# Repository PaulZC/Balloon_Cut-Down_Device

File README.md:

# Balloon_Cut-Down_Device

A cut-down device suitable for use on High Altitude Balloons and other remote actuation projects.

Designed to be triggered by the [Iridium Beacon Radio Board](https://github.com/PaulZC/Iridium_Beacon_Radio_Board),
carried by the [Iridium 9603N V5 Beacon](https://github.com/PaulZC/Iridium_9603_Beacon), the cut-down will be triggered
when it receives its own (unique) serial number on the chosen radio channel. The number of cut-downs that could be
triggered by a single Iridium Beacon is essentially unlimited. The cut-down can also be configured to trigger at
a pre-defined altitude.

The device comprises:
- [Scott Archery Shark release aid](https://scottarchery.com/collections/releases/products/shark-release), actuated by a
- [HiTec HS-82MG servo](https://www.servoshop.co.uk/index.php?pid=HITHS82MG&area=Servo), controlled by the
- [LPRS eRIC4 or eRIC9 integrated radio module](http://www.lprs.co.uk/products/easyradio-ism-modules/eric-soc-rf-modules.html).
- The altitude is provided by a [u-blox CAM-M8Q GNSS receiver](https://www.u-blox.com/en/product/cam-m8-series)

See [LEARN.md](https://github.com/PaulZC/Balloon_Cut-Down_Device/blob/master/LEARN.md) for further details.

See [SERVO.md](https://github.com/PaulZC/Balloon_Cut-Down_Device/blob/master/SERVO.md) for details on how to modify the HiTec servo for
high altitude operation.

See [SHARK.md](https://github.com/PaulZC/Balloon_Cut-Down_Device/blob/master/SHARK.md) for details on how to incorporate the Scott Archery Shark release aid
into the Cut-Down Device.

See [ASSEMBLY.md](https://github.com/PaulZC/Balloon_Cut-Down_Device/blob/master/ASSEMBLY.md) for details on how to assemble the PCB and the device itself.

See [CONFIGURE.md](https://github.com/PaulZC/Balloon_Cut-Down_Device/blob/master/CONFIGURE.md) for details on how to configure the servo positions and altitude limit.

See [Balloon_Cut-Down_Device.pdf](https://github.com/PaulZC/Balloon_Cut-Down_Device/blob/master/Balloon_Cut-Down_Device.pdf) for the schematic,
layout and Bill Of Materials.

The [Eagle](https://github.com/PaulZC/Balloon_Cut-Down_Device/tree/master/Eagle) directory contains the schematic and pcb design files.

The [eRIC](https://github.com/PaulZC/Balloon_Cut-Down_Device/tree/master/eRIC) directory contains the code for the eRIC integrated radio module.

The [Drawings](https://github.com/PaulZC/Balloon_Cut-Down_Device/tree/master/Drawings) directory contains the drawings for the trigger linkage.

If you have found this project useful and if you are able to, please cite the paper:

P. Clark et al, An open source toolkit for the tracking, termination and recovery of high altitude balloon flights and payloads, 2019 JINST 14 P04003
[DOI:10.1088/1748-0221/14/04/P04003](https://doi.org/10.1088/1748-0221/14/04/P04003)

The Accepted Manuscript is available on arXiv: http://arxiv.org/abs/1904.04321

This project is distributed under a Creative Commons Attribution + Share-alike (BY-SA) licence.
Please refer to section 5 of the licence for the "Disclaimer of Warranties and Limitation of Liability".

Enjoy!

**_Paul_**

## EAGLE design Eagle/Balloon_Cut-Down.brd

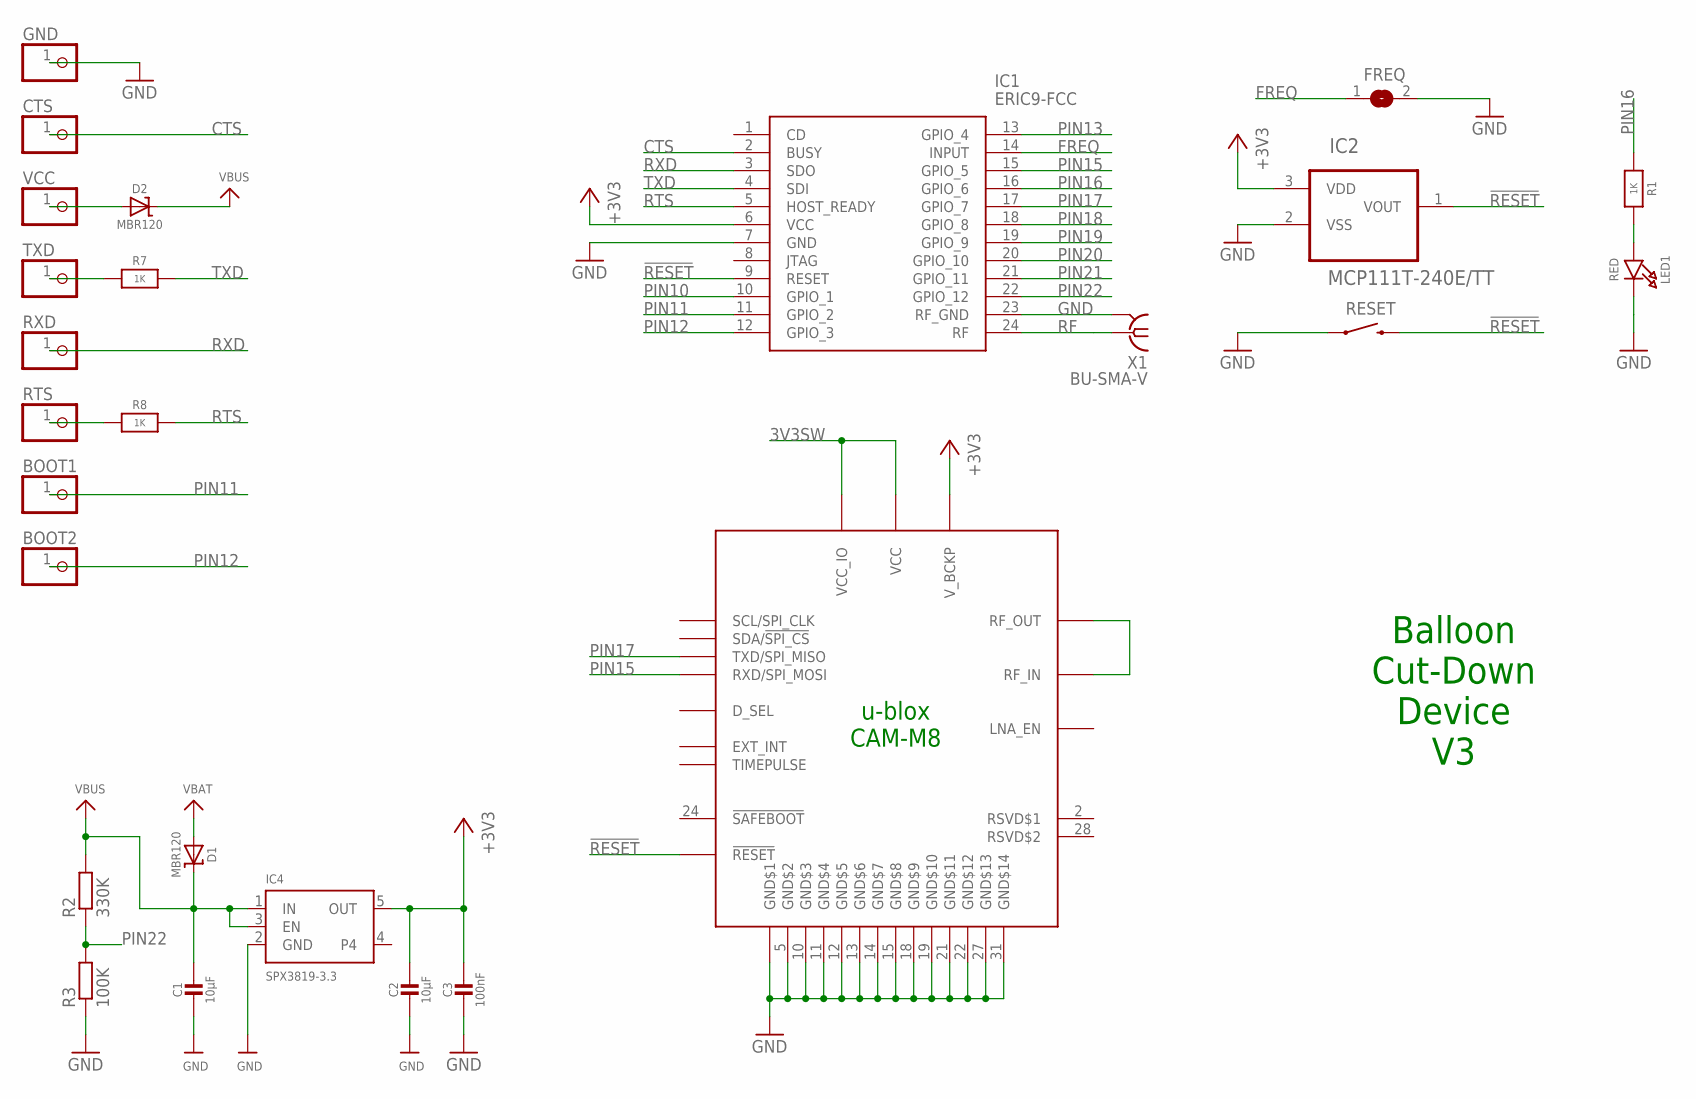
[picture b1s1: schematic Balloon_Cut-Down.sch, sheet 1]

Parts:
BOOT1, BOOT2: PINHD-1X1; 1X01
C1, C2: 10µF; 0805-NO
C3: 100nF; 0603-NO
CTS: PINHD-1X1; 1X01
D1, D2: MBR120; SOD-123
FREQ: SOLDERJUMPER; SOLDERJUMPER_ARROW_NOPASTE
GND: PINHD-1X1; 1X01
IC1: ERIC9-FCC; ERIC4
IC2: MCP111T-240E/TT; SOT95P237X112-3N; MPN MCP111T-240E/TT
IC3: CAM-M8
IC4: SPX3819-3.3; SOT23-5
LED1: RED; CHIPLED_0805_NOOUTLINE
R1, R7, R8: 1K; 0603-NO
R2: 330K; R0603
R3: 100K; R0603
RESET: SWITCH-MOMENTARY-2PTH; TACTILE-PTH
RTS: PINHD-1X1; 1X01
RXD: PINHD-1X1; 1X01
TXD: PINHD-1X1; 1X01
VCC: PINHD-1X1; 1X01
X1: BU-SMA-V

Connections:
3V3SW: IC3.1 (VCC_IO), IC3.9 (VCC); also elsewhere on the board
!RESET: IC1.9 (RESET), IC2.1 (VOUT), IC3.23 (!RESET), RESET.3 (2)
+3V3: C2.1, C3.1, IC1.6 (VCC), IC2.3 (VDD), IC3.8 (V_BCKP), IC4.5 (OUT); also elsewhere on the board
CTS: CTS.1, IC1.2 (BUSY); also elsewhere on the board
FREQ: FREQ.1, IC1.14 (INPUT)
GND: C1.2, C2.2, C3.2, FREQ.2, GND.1, IC1.7 (GND), IC1.23 (RF_GND), IC2.2 (VSS), IC3.4 (GND$1), IC3.5 (GND$2), IC3.10 (GND$3), IC3.11 (GND$4), IC3.12 (GND$5), IC3.13 (GND$6), IC3.14 (GND$7), IC3.15 (GND$8), IC3.18 (GND$9), IC3.19 (GND$10), IC3.21 (GND$11), IC3.22 (GND$12), IC3.27 (GND$13), IC3.31 (GND$14), IC4.2 (GND), LED1.C, R3.1, RESET.1, X1.2, X1.3 (2), X1.4 (2), X1.5 (2); also elsewhere on the board
unnamed: R7.1, TXD.1
unnamed: IC3.16 (RF_OUT), IC3.17 (RF_IN)
unnamed: LED1.A, R1.2
unnamed: R8.1, RTS.1
unnamed: D2.A, VCC.1
PIN10: IC1.10 (GPIO_1); also elsewhere on the board
PIN11: BOOT1.1, IC1.11 (GPIO_2)
PIN12: BOOT2.1, IC1.12 (GPIO_3)
PIN13: IC1.13 (GPIO_4); also elsewhere on the board
PIN15: IC1.15 (GPIO_5), IC3.26 (RXD/SPI_MOSI)
PIN16: IC1.16 (GPIO_6), R1.1
PIN17: IC1.17 (GPIO_7), IC3.25 (TXD/SPI_MISO)
PIN18: IC1.18 (GPIO_8); also elsewhere on the board
PIN19: IC1.19 (GPIO_9)
PIN20: IC1.20 (GPIO_10)
PIN21: IC1.21 (GPIO_11)
PIN22: IC1.22 (GPIO_12), R2.1, R3.2
RF: IC1.24 (RF), X1.1
RTS: IC1.5 (HOST_READY), R8.2; also elsewhere on the board
RXD: IC1.3 (SDO), RXD.1; also elsewhere on the board
TXD: IC1.4 (SDI), R7.2; also elsewhere on the board
VBAT: D1.A; also elsewhere on the board
VBUS: C1.1, D1.C, D2.C, IC4.1 (IN), IC4.3 (EN), R2.2

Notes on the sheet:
Balloon Cut-Down Device V3
u-blox CAM-M8

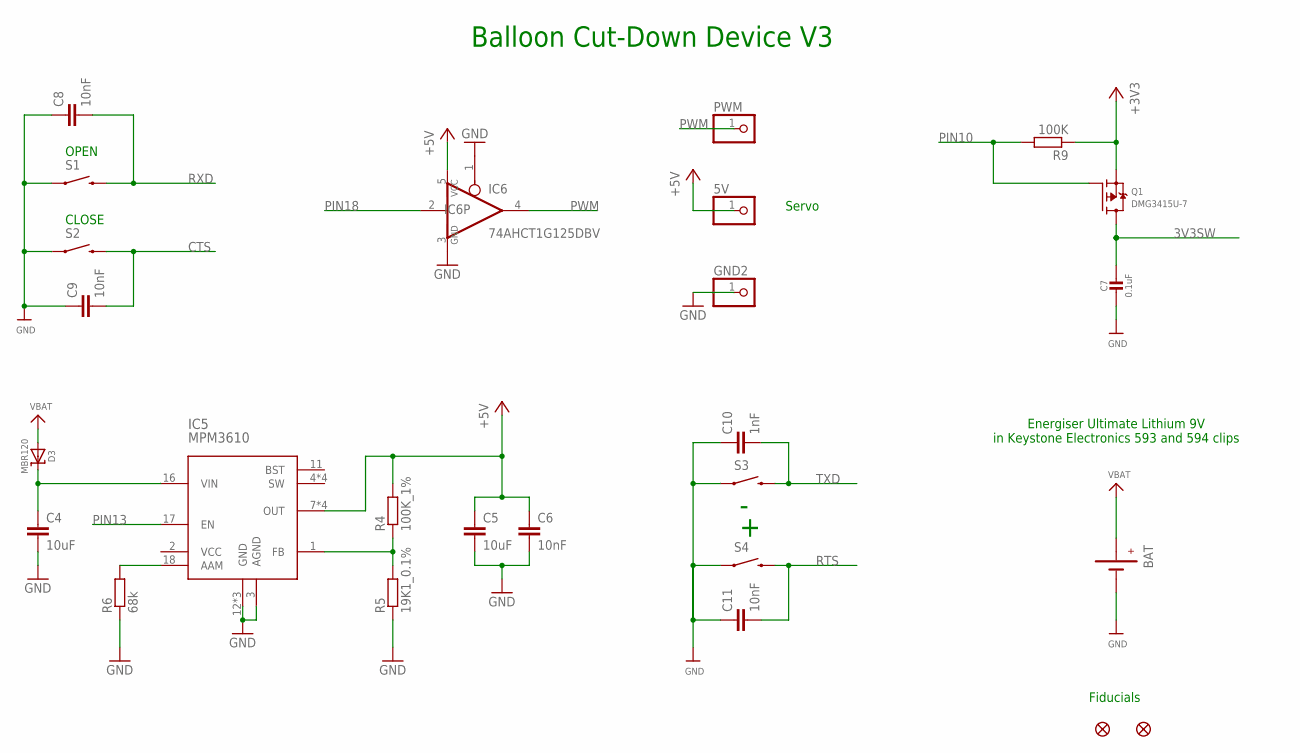
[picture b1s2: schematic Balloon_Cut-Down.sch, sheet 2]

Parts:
5V: PINHD-1X1; 1X01
BAT: BATTERYBATTERY-9V-KEYSTONE-593-594; BATTERY-9V-KEYSTONE-593-594
C4, C5: 10uF; C0805
C6, C8, C9, C11: 10nF; C0805
C7: 0.1uF; 0805-NO
C10: 1nF; C0805
D3: MBR120; SOD-123
FD1, FD2: FIDUCIAL1X2; FIDUCIAL-1X2
GND2: PINHD-1X1; 1X01
IC5: MPM3610; QFN-20
IC6: 74AHCT1G125DBV; SOT23-5
PWM: PINHD-1X1; 1X01
Q1: DMG3415U-7; SOT23-WIDE
R4: 100K_1%; R0805
R5: 19K1_0.1%; R0805
R6: 68k; R0805
R9: 100K; R0603
S1, S2, S3, S4: SWITCH-MOMENTARY-2PTH; TACTILE-PTH

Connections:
3V3SW: C7.1, Q1.3 (D); also elsewhere on the board
+3V3: Q1.2 (S), R9.1; also elsewhere on the board
+5V: 5V.1, C5.1, C6.1, IC5.7 (OUT), IC5.8 (OUT), IC5.9 (OUT), IC5.20 (OUT), IC6.5 (VCC), R4.2
CTS: C9.2, S2.3 (2); also elsewhere on the board
GND: BAT.GND (-), BAT.GND1 (-), BAT.GND2 (-), C4.2, C5.2, C6.2, C7.2, C8.1, C9.1, C10.1, C11.1, GND2.1, IC5.3 (AGND), IC5.12 (GND), IC5.13 (GND), IC5.14 (GND), IC6.1 (OE), IC6.3 (GND), R5.1, R6.1, S1.1, S2.1, S3.1, S4.1; also elsewhere on the board
unnamed: C4.1, D3.C, IC5.16 (VIN)
unnamed: IC5.1 (FB), R4.1, R5.2
unnamed: IC5.18 (AAM), R6.2
PIN10: Q1.1 (G), R9.2; also elsewhere on the board
PIN13: IC5.17 (EN); also elsewhere on the board
PIN18: IC6.2 (I); also elsewhere on the board
PWM: IC6.4 (O), PWM.1
RTS: C11.2, S4.3 (2); also elsewhere on the board
RXD: C8.2, S1.3 (2); also elsewhere on the board
TXD: C10.2, S3.3 (2); also elsewhere on the board
VBAT: BAT.PWR (+), BAT.PWR1 (+), BAT.PWR2 (+), D3.A; also elsewhere on the board

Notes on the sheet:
Energiser Ultimate Lithium 9V in Keystone Electronics 593 and 594 clips
Balloon Cut-Down Device V3
Fiducials
Servo
OPEN
CLOSE

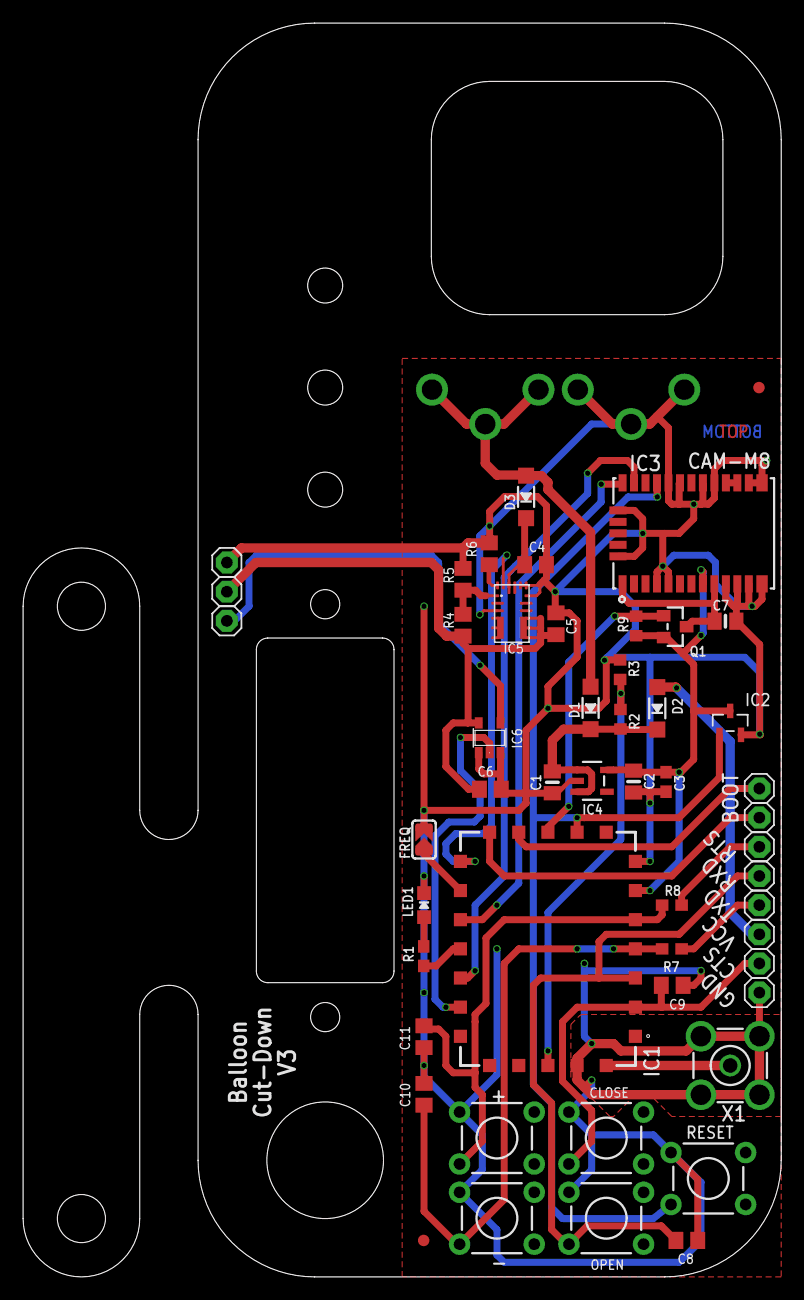
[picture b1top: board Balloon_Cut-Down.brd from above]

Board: 2 copper layers, 66.0 x 109.2 mm, 52 parts (1 on the bottom side), 31 nets.

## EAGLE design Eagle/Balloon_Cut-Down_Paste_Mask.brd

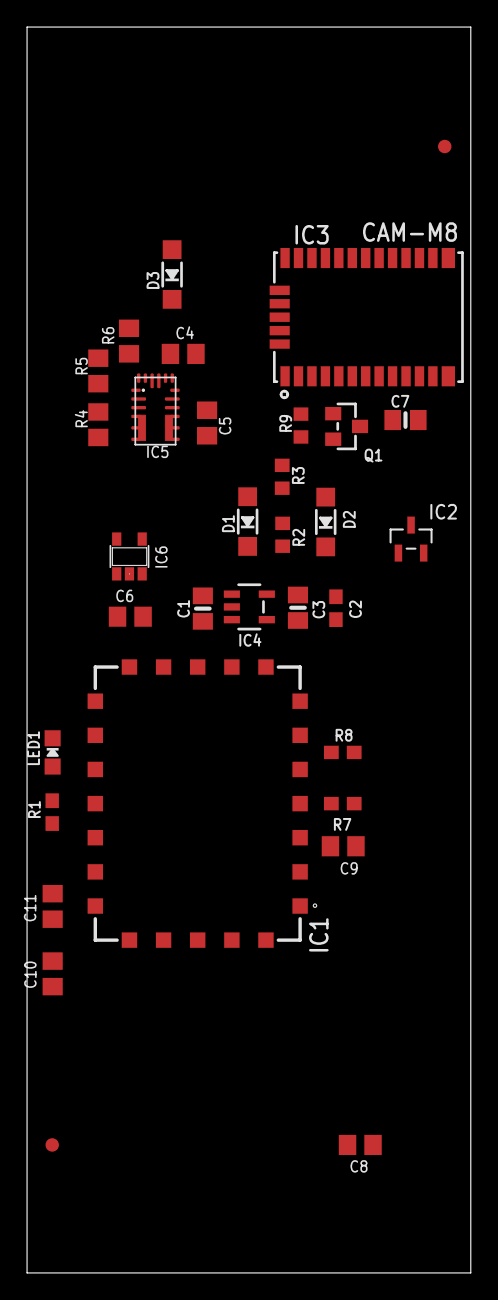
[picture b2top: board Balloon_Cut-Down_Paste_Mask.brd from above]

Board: 2 copper layers, 33.0 x 92.7 mm, 33 parts (0 on the bottom side), 2 nets, no tracks yet.

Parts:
C1, C2: 10µF; 0805-NO
C3: 100nF; 0603-NO
C4, C5: 10uF; C0805
C6, C8, C9, C10, C11: 10nF; C0805
C7: 0.1uF; 0805-NO
D1, D2, D3: MBR120; SOD-123
FD1, FD2: FIDUCIAL1X2; FIDUCIAL-1X2
IC1: ERIC9-FCC; ERIC4
IC2: MCP111T-240E/TT; SOT95P237X112-3N
IC3: CAM-M8
IC4: SPX3819-3.3; SOT23-5
IC5: MPM3610; QFN-20
IC6: 74AHCT1G125DBV; SOT23-5
LED1: RED; CHIPLED_0805_NOOUTLINE
Q1: DMG3415U-7; SOT23-WIDE
R1, R7, R8: 1K; 0603-NO
R2: 330K; R0603
R3, R9: 100K; R0603
R4: 100K_1%; R0805
R5: 19K1_0.1%; R0805
R6: 68k; R0805

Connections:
GND: IC4.2, IC6.3
VCC: IC3.9, IC6.5

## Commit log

2018-06-11 Major update
2018-06-14 Added more images and animated gifs
2018-06-14 Corrections...
2018-06-16 Corrected an image link
2018-06-23 Updated the wiring diagram
2018-08-08 Updated trigger block drawings
2018-12-11 Major update for the V3 PCB
    Major update for the V3 PCB: the cut-down is now based on the eRIC4 or eRIC9 radio controller and can be triggered by radio; a u-blox CAM-M8Q provides altitude information; the Shark and Servo are no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
2018-12-11 Minor corrections
2018-12-12 Minor updates
    Added an extra 1 sec delay in the eRIC code to allow the serial number to be transmitted correctly following the eRIC_RadioUpdate
2019-04-10 Added the citation

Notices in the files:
parts and their libraries:
microbuilder: This work is placed in the public domain, and may be freely used for commercial and non-commercial work with the following conditions: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
SparkFun-Electromechanical: Licensing: Creative Commons ShareAlike 4.0 International - https://creativecommons.org/licenses/by-sa/4.0
